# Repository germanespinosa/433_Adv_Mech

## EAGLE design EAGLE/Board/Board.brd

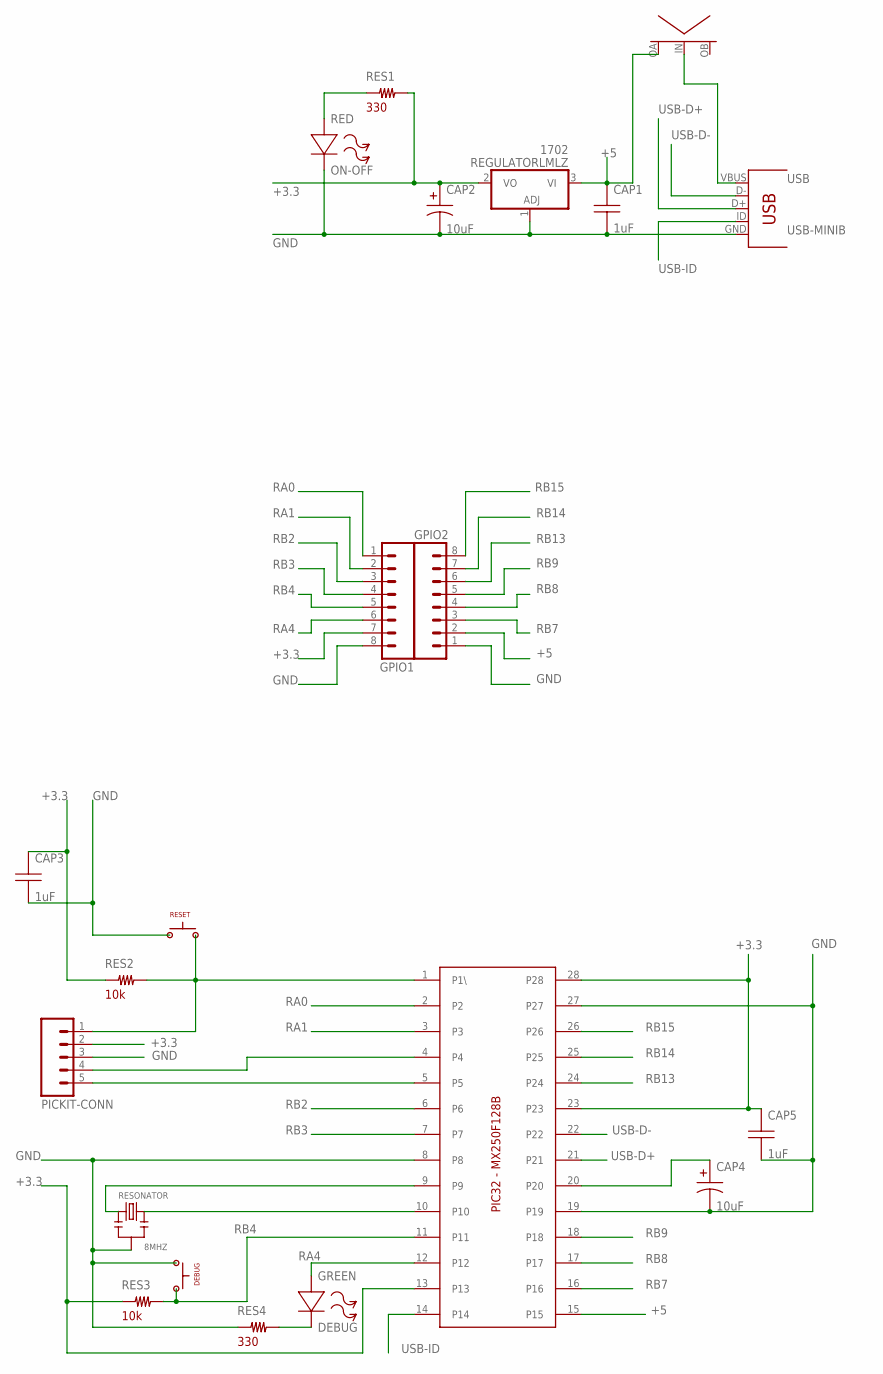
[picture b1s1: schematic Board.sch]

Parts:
1702: REGULATORLMLZ; TO92
CAP1, CAP3, CAP5: 1uF; CAP-CERAMIC
CAP2, CAP4: 10uF; TT2D4
DEBUG: BUTTON; PUSH5
GPIO1, GPIO2: M08; 1X08_ROUND
GREEN: DEBUG; LED
PIC32-MX250F128B: PIC32-MX250F128B; DIL28-3
PICKIT-CONN: CONNECTOR-5PINPTH; CONNECTOR-5PIN
RED: ON-OFF; LED
RES1, RES4: 330; RESISTOR-7MM
RES2, RES3: 10k; RESISTOR-7MM
RESET: BUTTON; PUSH5
RESONATOR: 8MHZ; OSCILATOR-CRYSTAL
U$1: SWITCH
USB: USB-MINIB; USB-MB-H

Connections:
+3.3: 1702.2 (VO), CAP2.+, CAP3.1 (A), CAP5.1 (A), GPIO1.7, PIC32-MX250F128B.13, PIC32-MX250F128B.23, PIC32-MX250F128B.28, PICKIT-CONN.2, RES1.2, RES2.1, RES3.1
+5: 1702.3 (VI), CAP1.1 (A), GPIO2.2, PIC32-MX250F128B.15, U$1.OA
GND: 1702.1 (ADJ), CAP1.2 (B), CAP2.-, CAP3.2 (B), CAP4.-, CAP5.2 (B), DEBUG.1, GPIO1.8, GPIO2.1, PIC32-MX250F128B.8, PIC32-MX250F128B.19, PIC32-MX250F128B.27, PICKIT-CONN.3, RED.-, RES4.1, RESET.1, RESONATOR.2, USB.GND
unnamed: PIC32-MX250F128B.10, RESONATOR.3
unnamed: PIC32-MX250F128B.9, RESONATOR.1
unnamed: RED.+, RES1.1
unnamed: PIC32-MX250F128B.4, PICKIT-CONN.4
unnamed: CAP4.+, PIC32-MX250F128B.20
unnamed: GREEN.-, RES4.2
unnamed: PIC32-MX250F128B.1 (P1\), PICKIT-CONN.1, RES2.2, RESET.2
unnamed: U$1.IN, USB.VBUS
unnamed: PIC32-MX250F128B.5, PICKIT-CONN.5
RA0: GPIO1.1, PIC32-MX250F128B.2
RA1: GPIO1.2, PIC32-MX250F128B.3
RA4: GPIO1.6, GREEN.+, PIC32-MX250F128B.12
RB2: GPIO1.3, PIC32-MX250F128B.6
RB3: GPIO1.4, PIC32-MX250F128B.7
RB4: DEBUG.2, GPIO1.5, PIC32-MX250F128B.11, RES3.2
RB7: GPIO2.3, PIC32-MX250F128B.16
RB8: GPIO2.4, PIC32-MX250F128B.17
RB9: GPIO2.5, PIC32-MX250F128B.18
RB13: GPIO2.6, PIC32-MX250F128B.24
RB14: GPIO2.7, PIC32-MX250F128B.25
RB15: GPIO2.8, PIC32-MX250F128B.26
USB-D+: PIC32-MX250F128B.21, USB.D+
USB-D-: PIC32-MX250F128B.22, USB.D-
USB-ID: PIC32-MX250F128B.14, USB.ID

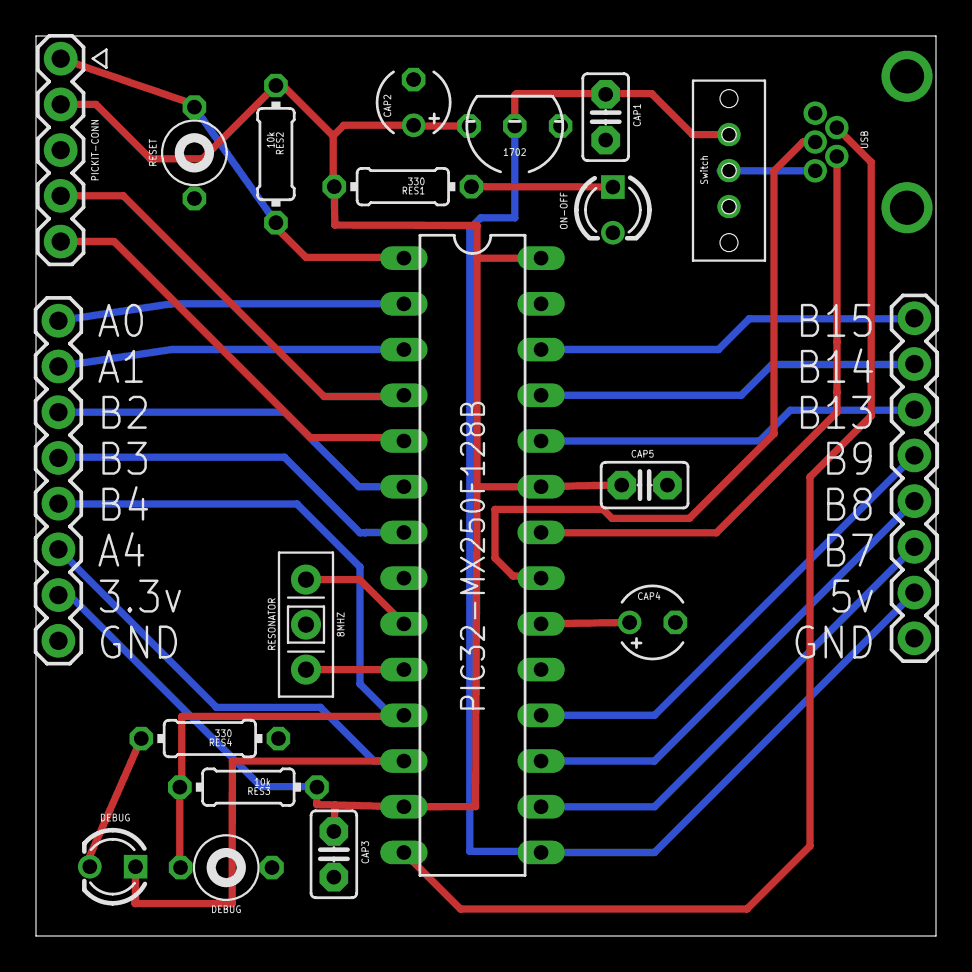
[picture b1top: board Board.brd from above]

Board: 2 copper layers, 50.0 x 50.0 mm, 21 parts (0 on the bottom side), 27 nets.

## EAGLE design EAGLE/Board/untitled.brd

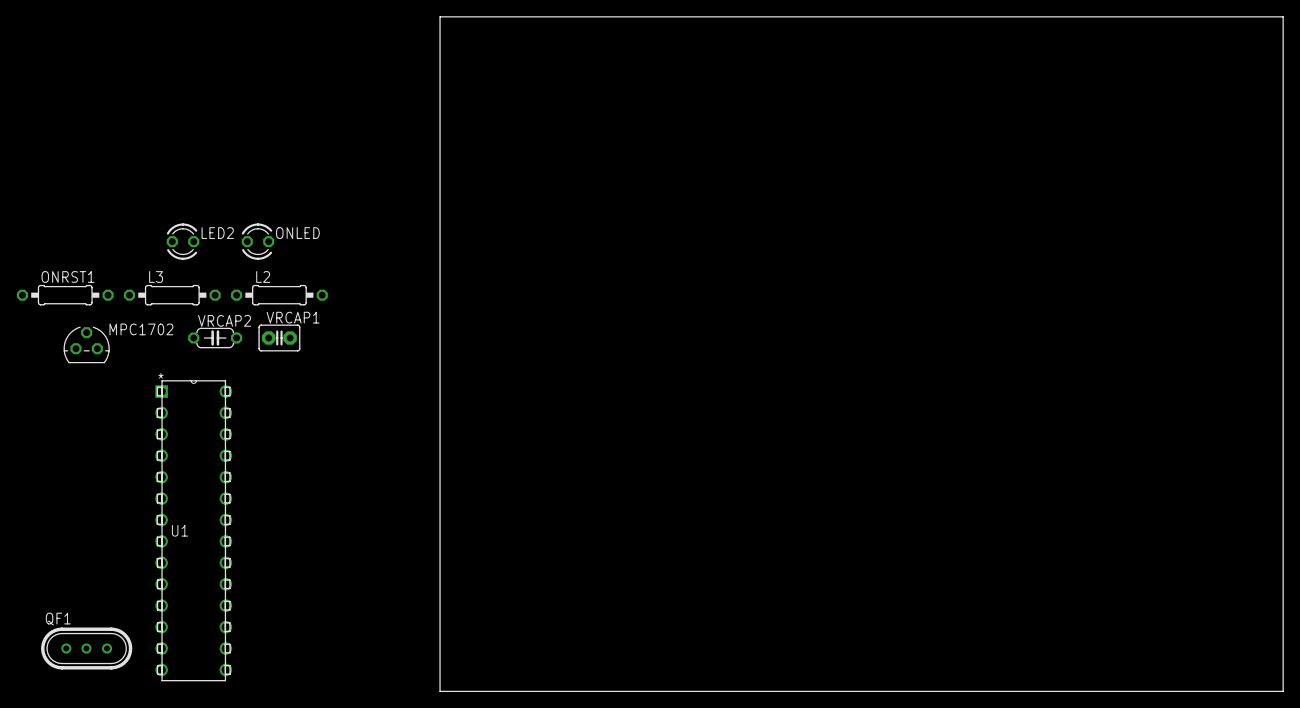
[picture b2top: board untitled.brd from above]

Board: 2 copper layers, 100.0 x 80.0 mm, 10 parts (0 on the bottom side), 4 nets, no tracks yet.

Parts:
L2, L3: 0207/10
LED2: LED3MM
MPC1702: LM317LZ; TO92
ONLED: LED3MM
ONRST1: 330; 0207/10
QF1: ECS-10.7-7.5A; HC49U
U1: PIC32MX250F128B-I_SP; SPDIP28_300MC
VRCAP1: 1; C2.5-3
VRCAP2: 10; C050-024X044

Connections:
unnamed: MPC1702.3, ONLED.K, VRCAP1.1, VRCAP2.2
unnamed: MPC1702.2, ONRST1.2, VRCAP2.1
unnamed: MPC1702.1, VRCAP1.2
unnamed: ONLED.A, ONRST1.1

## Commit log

2016-04-05 Hw1 - 1
    Circuit Strawman and Osciloscope pics
2016-04-05 breadboard
2016-04-05 project
2016-04-05 working
2016-04-06 works
2016-04-06 board
2016-04-07 working code
2016-04-07 oh my
2016-04-08 library
2016-04-08 lib ok
2016-04-08 tantalum capacitor
2016-04-09 schematics ready
2016-04-13 gerber files
2016-04-28 HW4 done
2016-05-05 HW7 done
2016-05-05 hw7 update
2016-05-09 all working
2016-05-09 imu_file
2016-05-17 Libraries
2016-05-18 HW4 lib
2016-05-18 lcd_printf
2016-06-01 ROBOT
